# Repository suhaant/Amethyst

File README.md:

<div align="center">

### Smart wound care that catches infection early and treats it on the spot.

A wearable patch that senses infection before you can see it, scores the risk with an ML model,
has an AI agent check the evidence, and treats with **low-frequency ultrasound** and **405 nm violet light**.

**[Watch the 40-second film](remotion/renders/AmethystFilm.mp4)** · [How it works](#how-it-works) · [Quick start](#quick-start) · [The math](#the-math) · [Safety](#safety-in-three-layers)

</div>

---

## The problem

**60%** of diabetic foot ulcers become infected, and **15–20%** of diabetic foot infections end in amputation. Nerve damage removes pain, the body's warning sign, so infection often goes unnoticed until it's visible, and by then it's serious.

The early signs are measurable long before that. Infected wounds turn **alkaline** (healthy wounds sit at pH 4–6; infected ones at 7.5–9), get **warmer** and **wetter**, and bacteria use up the **glucose** in wound fluid. Amethyst watches for exactly those changes.

<sub>Sources: Diabetes Care; Nussbaum et al., *Value in Health* 2018. More in [`hardware/research/`](hardware/research/).</sub>

## How it works

```mermaid
flowchart LR
    P["Amethyst patch<br/>pH · moisture · 3× temp"] -->|"BLE, every 30 min"| S
    C["CGM<br/>blood glucose"] --> S
    S["FastAPI server<br/>POST /api/readings"] --> A{{"Gemini agent"}}
    A -->|tool| M["XGBoost model<br/>risk = likelihood × severity"]
    A -->|tool| D["Dosing engine<br/>tiers + safety caps"]
    A --> F["Notes, fact-checked<br/>in code"]
    S --> App["Expo app<br/>alert · therapy · trends"]
    S --> DB[("Databricks<br/>care record + dashboard")]
    D -->|"therapy command"| P
```

1. **Sense.** Every 30 minutes the patch reads wound pH, moisture (impedance) and temperature at three spots (wound edge, healthy reference skin, ambient). Blood glucose comes from the wearer's CGM.
2. **Predict.** An XGBoost model compares each reading with the patient's **own first-day baseline** and outputs a 0–100 risk score and a tier: monitor, watch, treat or intensive.
3. **Reason.** A **Gemini agent** calls the model and the dosing engine as tools, then writes a clinician-ready assessment. It covers the trend, sensor faults, signals that disagree with the model, its confidence, and whether a clinician should look. **It never invents a number:** risk and doses always come from our code, and its notes are fact-checked against the tool results.
4. **Treat.** In the treat tier the patch runs ultrasound to break up biofilm, then 405 nm light to kill bacteria. Lower tiers get gentle healing ultrasound and closer monitoring.
5. **Alert.** The app shows the patient their risk, trends and therapy. Every reading and assessment lands in Databricks for the care team.

## Results

Validated **leave-one-person-out** (16 folds): every person is scored by a model that never saw their data.

| | Random forest | **XGBoost** (shipped) |
|---|---|---|
| AUC | 0.976 | **0.978** |
| Brier skill score | 0.834 | **0.845** |
| Infected wounds detected | 100% | **100%** |
| Median hours from onset to alarm | 30.3 | **27.2** |
| False alarms, clean wounds | **0.3%** | 2.1% |
| Model size | 11.9 MB | **3.1 MB** |
| Time per prediction | 12.4 ms | **0.14 ms** |

We shipped XGBoost: it alarms **3.1 h earlier** and is **3.8× smaller** and **89× faster**, which matters on a wearable. The extra false alarms are absorbed by risk smoothing and the agent's review.

Which sensors matter most (AUC of each sensor on its own): **moisture 0.952** · temperature 0.933 · pH 0.917 · wound glucose 0.886 · blood glucose 0.650 · pH + temp + moisture together **0.976**.

> All results are on simulated data (see [limits](#honest-limits)). The full method is in [`docs/ml-pipeline.md`](docs/ml-pipeline.md).

## The math

**Training data.** No public dataset of continuous wound-sensor readings with infection labels exists, so we simulated one from **30+ published studies** and **real Dexcom glucose traces from 16 people** (PhysioNet):

$$600 \text{ wounds} \times 14 \text{ days} \times 48 \text{ readings/day} = 403{,}200 \text{ labelled readings}$$

**Features.** 5 signals × (6 h median, change vs. day-1 baseline, 6 h change, 24 h change, 24 h std) + 2 time-of-day terms = **27 features**.

**Risk = likelihood × severity.** Trained on cleanly separated data, the classifier is near-certain for *any* sustained shift. So we scale its probability by how far the signs have actually moved toward a full infection:

$$p = P(\text{warning}) + P(\text{infection})$$

$$s = \text{mean of the 3 largest of } \left\lbrace \frac{\Delta \text{pH}}{0.65},\ \ \frac{\Delta T}{1.6^{\circ}\text{C}},\ \ \frac{-\Delta \ln Z}{-\ln 0.65},\ \ \frac{-\Delta g / g_0}{0.40}\right\rbrace$$

Each Δ is a 2 h median minus the patient's day-1 baseline. The denominators are a full infection's average effect in the simulator: pH +0.65, temperature +1.6 °C, impedance −35%, wound glucose −40%. Each term is clipped to [0, 1.25] and *s* to [0, 1]. Using the top 3 of 4 means a wound whose pH doesn't rise, which happens in real infections, still scores. The score is then smoothed so one noisy reading can't trigger treatment (τ = 3 h, Δt = 0.5 h):

$$R_t = R_{t-1} + \alpha(100 p_t s_t - R_{t-1}), \qquad \alpha = \frac{0.5}{3 + 0.5} \approx 0.143$$

**Tiers** use 10-point hysteresis: each is entered at its threshold and left only 10 points below it, so the device doesn't flicker.

| Tier | Enter at | Therapy each 8 h session (3/day) |
|---|---|---|
| 0 · Monitor | — | 1.5 MHz healing ultrasound, 6.7 min (20 min/day ÷ 3) |
| 1 · Watch | 30 | Healing ultrasound + closer monitoring |
| 2 · Treat | 55 | Ultrasound to break biofilm → 405 nm light |
| 3 · Intensive | 80 | Same, scaled up toward the caps |

**Light dose** (treat tier and above) at 10 mW/cm², with the 36 J/cm² daily cap split over 3 sessions:

$$x = \text{clip}\left(\frac{R - 30}{60}, 0, 1\right), \qquad E = 12x \ \text{J/cm}^2, \qquad t = \frac{E}{0.010 \ \text{W/cm}^2}$$

**Ultrasound** (treat tier and above), run before the light:

$$y = \text{clip}\left(\frac{R - 55}{35}, 0, 1\right), \qquad t_{\text{US}} = \max(4,\ 10y) \ \text{min}, \qquad I = 0.1 + 0.4y \ \text{W/cm}^2$$

| Risk *R* | Light | Ultrasound |
|---|---|---|
| 55 (enters treat) | 5 J/cm² → **8.3 min** | 4 min at 0.10 W/cm² |
| 72.5 | 8.5 J/cm² → **14.2 min** | 5 min at 0.30 W/cm² |
| 100 | 12 J/cm² → **20 min** (3 × 12 = 36 J/cm²/day cap) | 10 min at 0.50 W/cm² |

## The AI agent

[`wound_agent/`](wound_agent/) wraps the model and dosing in three tools: `get_sensor_history` → `predict_infection` → `plan_treatment`. The LLM writes structured notes: `summary`, `trend`, `reasoning`, `data_quality_flags`, `conflicting_signals`, `recommend_clinician_review` and `confidence`.

- **Gemini by default.** Gemini 3.8 Flash with low thinking takes about 5 s and about $0.005 per assessment. `GEMINI_MODEL=gemini-3.1-pro-preview` with `GEMINI_THINKING=high` gives maximum care. OpenRouter and Claude Opus also work (`AGENT_PROVIDER=gemini|openrouter|claude`).
- **Fact-checked.** After the agent writes, code checks its notes against the tool results (risk score, tier, lifted patch, clinician review) and asks for one correction if anything is off.
- **Knows what to distrust.** It's told each sensor's standalone accuracy, that infections don't always raise pH, and how hysteresis works. In testing it caught a 43 °C reading as a sensor fault rather than a fever, and blamed a risk jump on a meal-time glucose spike while the wound sensors stayed healthy.
- **Never blocks the demo.** With no API key, the same model and dosing run and a rule-based summary stands in.

## Hardware

A reusable **30 × 40 mm, 4-layer** pod that clips onto a disposable hydrogel pad. [Full spec →](hardware/docs/board-spec.md)

| Block | Parts |
|---|---|
| Radio + MCU | Raytac MDBT42Q (nRF52832), Bluetooth LE |
| Temperature | 3× TMP117: wound edge, reference skin, ambient |
| Moisture | 1 kHz square wave through a 47 kΩ reference into the pad electrodes, read as impedance (no dedicated chip) |
| pH | AD8603 buffer on the working electrode |
| Light | 6× 405 nm LEDs, TPS61165 constant-current boost, PWM dimming |
| Ultrasound | 15 mm 30 kHz piezo disc, TPS61040 boost (5–10 V) + DRV8837 H-bridge + 4.7 mH resonant inductor |
| Power | Single LiPo, MCP73831 charger, AP2112K 3.3 V regulator |
| Extras | Pad-ID resistor, button for a daily pain/odour check-in, SWD debug pads |

**Generated, not drawn.** One Python file ([`design.py`](hardware/kicad/gen/design.py)) generates the schematic, places every part, autoroutes all **178 connections** and runs KiCad's electrical and design-rule checks in one command.

**Power and heat budget** ([details](hardware/experiments/out/power_thermal_results.md)):
- Sensing averages **~22 µA**, which is about **60 days on a 40 mAh cell**.
- At 10 mW/cm² of light, skin reaches 37.3 °C, or **38.7 °C on a poorly perfused diabetic foot**, including the LEDs' own heat. Both stay under our 41 °C ceiling.
- Doubling to 20 mW/cm² would hit 43.4 °C, so we didn't.

## Safety in three layers

| Layer | What it enforces |
|---|---|
| **1 · Software** ([`risk_to_dose.py`](risk_to_dose.py)) | Dose caps, tier hysteresis, no therapy when impedance > 150 kΩ (patch lifted) |
| **2 · Firmware** ([`firmware/`](firmware/)) | The same caps again, whatever the phone asks: 10 mW/cm², 36 J/cm²/day, 10 min of pulsed ultrasound (500 ms on / off), stop at 41 °C, and no session without a pad attached and on the skin, a working wound sensor, and battery > 3.5 V |
| **3 · Hardware** | Every TMP117 alert pin feeds AND gates on the light and ultrasound enables. At **42 °C**, therapy cuts out **even if the firmware has crashed** |

## Quick start

**Python 3.12+** (Adam's pinned numpy 2.5 and xgboost 3.4 need it).

```bash
python -m venv .venv
source .venv/bin/activate          # Windows: .venv\Scripts\activate
pip install -r requirements.txt
cp .env.example .env               # add GEMINI_API_KEY (or OPENROUTER_ / ANTHROPIC_API_KEY)
```

**Run the agent on a simulated wound:**

```bash
python main.py -v --scenario infected        # healthy | early_infection | infected | sensor_fault | patch_lifted
python main.py --history sample_data/simulated_wound_history.csv
python main.py --offline                     # model + dosing only, no LLM
```

**Live demo + hardware API** (then open http://localhost:8000):

```bash
python demo_ui/server.py
python demo_ui/send_reading.py --scenario infection --count 8 --every 3    # pretend to be the patch
```

| Endpoint | What |
|---|---|
| `POST /api/readings` | One patch reading in → risk, tier and therapy plan out |
| `GET /api/state` | Latest assessment (the app polls this) |
| `GET /api/events` | Server-sent events for every pipeline step |
| `POST /api/reset` | New patient with a fresh 24 h baseline |
| `GET /docs` | Interactive API docs |

**Phone app** (Expo Go):

```bash
cd app && npm install && npx expo start      # add --tunnel on campus Wi-Fi
```

**Firmware tests** (simulated board) and **board build** (KiCad 10):

```bash
cd firmware && make test && make arm-check
cd hardware/kicad && ./build.sh              # about 6 min with autorouting; --no-route for seconds
```

**Databricks care record** (landing from the `databricks` branch; design in [`docs/superpowers/specs/`](docs/superpowers/specs/)):

```bash
python main.py --databricks                  # readings + assessments to Databricks, care-team dashboard
```

**Film:**

```bash
cd remotion && npm install && npm run dev
```

**Tests:**

```bash
python -m pytest
```

## Repo map

| Path | What |
|---|---|
| [`wound_agent/`](wound_agent/) · [`main.py`](main.py) | AI agent: tools, prompts, providers, fact check, CLI |
| [`predict.py`](predict.py) · [`risk_to_dose.py`](risk_to_dose.py) · [`model/`](model/) | Trained XGBoost model, risk score, dosing engine |
| [`generate_data.py`](generate_data.py) · [`train_*.py`](train_final.py) · [`compare_models.py`](compare_models.py) | Simulator, training, RF vs. XGBoost, validation ([write-up](docs/ml-pipeline.md)) |
| [`research/`](research/) · [`hardware/research/`](hardware/research/) | Literature values for every simulator parameter, signal and dose, with sources |
| [`demo_ui/`](demo_ui/) | FastAPI server, hardware API, animated live demo |
| [`app/`](app/) | Expo companion app: Pair, Home, Alert, Therapy, Trends |
| [`hardware/`](hardware/) · [`firmware/`](firmware/) | KiCad board generator + board, C firmware with Zephyr port |
| [`remotion/`](remotion/) | Demo film and brand assets |
| [`tests/`](tests/) | Pipeline tests: scenarios, tiers, dose caps, interlock |

## Honest limits

- **Simulated training data.** The model has never seen a real wound. Retrain on real patch data before any clinical use.
- **Prototype doses** from published studies, not a validated medical protocol.
- **The board is designed and autorouted but not yet fabricated,** and the firmware has only run on a simulated board. Light and ultrasound intensity at the wound are estimates until measured.
- **Not all on the board yet.** The board's ultrasound runs at 30 kHz (within the 20–40 kHz range of clinical wound devices). The 1.5 MHz healing mode and wound-fluid glucose sensing aren't on this board yet.
- **Combining light and ultrasound** is backed by lab (in-vitro) studies so far.

## Team

Built at **WolfHacks 2026** by:
- **Adam Rakhmanov:** ML model, simulator, dosing, demo server.
- **Anay Vaidya:** hardware, firmware, Databricks.
- **Aarush:** app and film.
- **Suhaan Temkar:** AI agent.

<sub>Glucose data: BIG IDEAs Lab Glycemic Variability and Wearable Device Data v1.1.3, PhysioNet, ODC-By 1.0.</sub>

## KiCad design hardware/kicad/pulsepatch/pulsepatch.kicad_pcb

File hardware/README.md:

# PulsePatch hardware

Hardware for PulsePatch, a wearable wound patch that senses temperature, moisture and pH and can drive 405 nm light and low-frequency ultrasound. Owner: Anay. Lives on the `KiCAD` branch until it is ready for `main`.

## Layout

| Folder | What is in it |
|---|---|
| `context/` | The team synopsis (`Wolfhacks.pdf`) and the note on light plus ultrasound evidence |
| `research/raw/` | Literature reviews: `A-clinical-signals.md` (which wound signals are worth sensing) and `C-therapy-hardware.md` (light and ultrasound doses, parts, safety limits) |
| `experiments/` | Scripts and results: KiCad library scan, board packing, power and heat budget |
| `docs/board-spec.md` | The approved board spec and the list of things not verified yet |
| `kicad/gen/` | The generator. `design.py` is the single source of truth for parts, connections and placement |
| `kicad/pulsepatch/` | Generated KiCad project: schematic, board, check reports, renders |

## Build the board

Needs KiCad 10 at `/Applications/KiCad` and Java (for the autorouter).

```
cd hardware/kicad
./build.sh              # full build with autorouting, about 6 minutes
./build.sh --no-route   # placed, unrouted board in seconds
```

Then open `kicad/pulsepatch/pulsepatch.kicad_pro` in KiCad.

The build writes `erc.rpt` (schematic check), `drc.rpt` (board check), `pulsepatch-schematic.pdf`, and `render-top.png` / `render-bottom.png` into `kicad/pulsepatch/`.

## Changing the design

Edit `kicad/gen/design.py` and rebuild. The schematic and board are regenerated from it every time, so edits made by hand in the KiCad editor are lost on the next build. Once the design settles and hand routing starts, stop running the build and treat the KiCad files as the source.

## Status

See `docs/board-spec.md` for what is and is not verified. The board is autorouted and has not been reviewed by a person or fabricated.

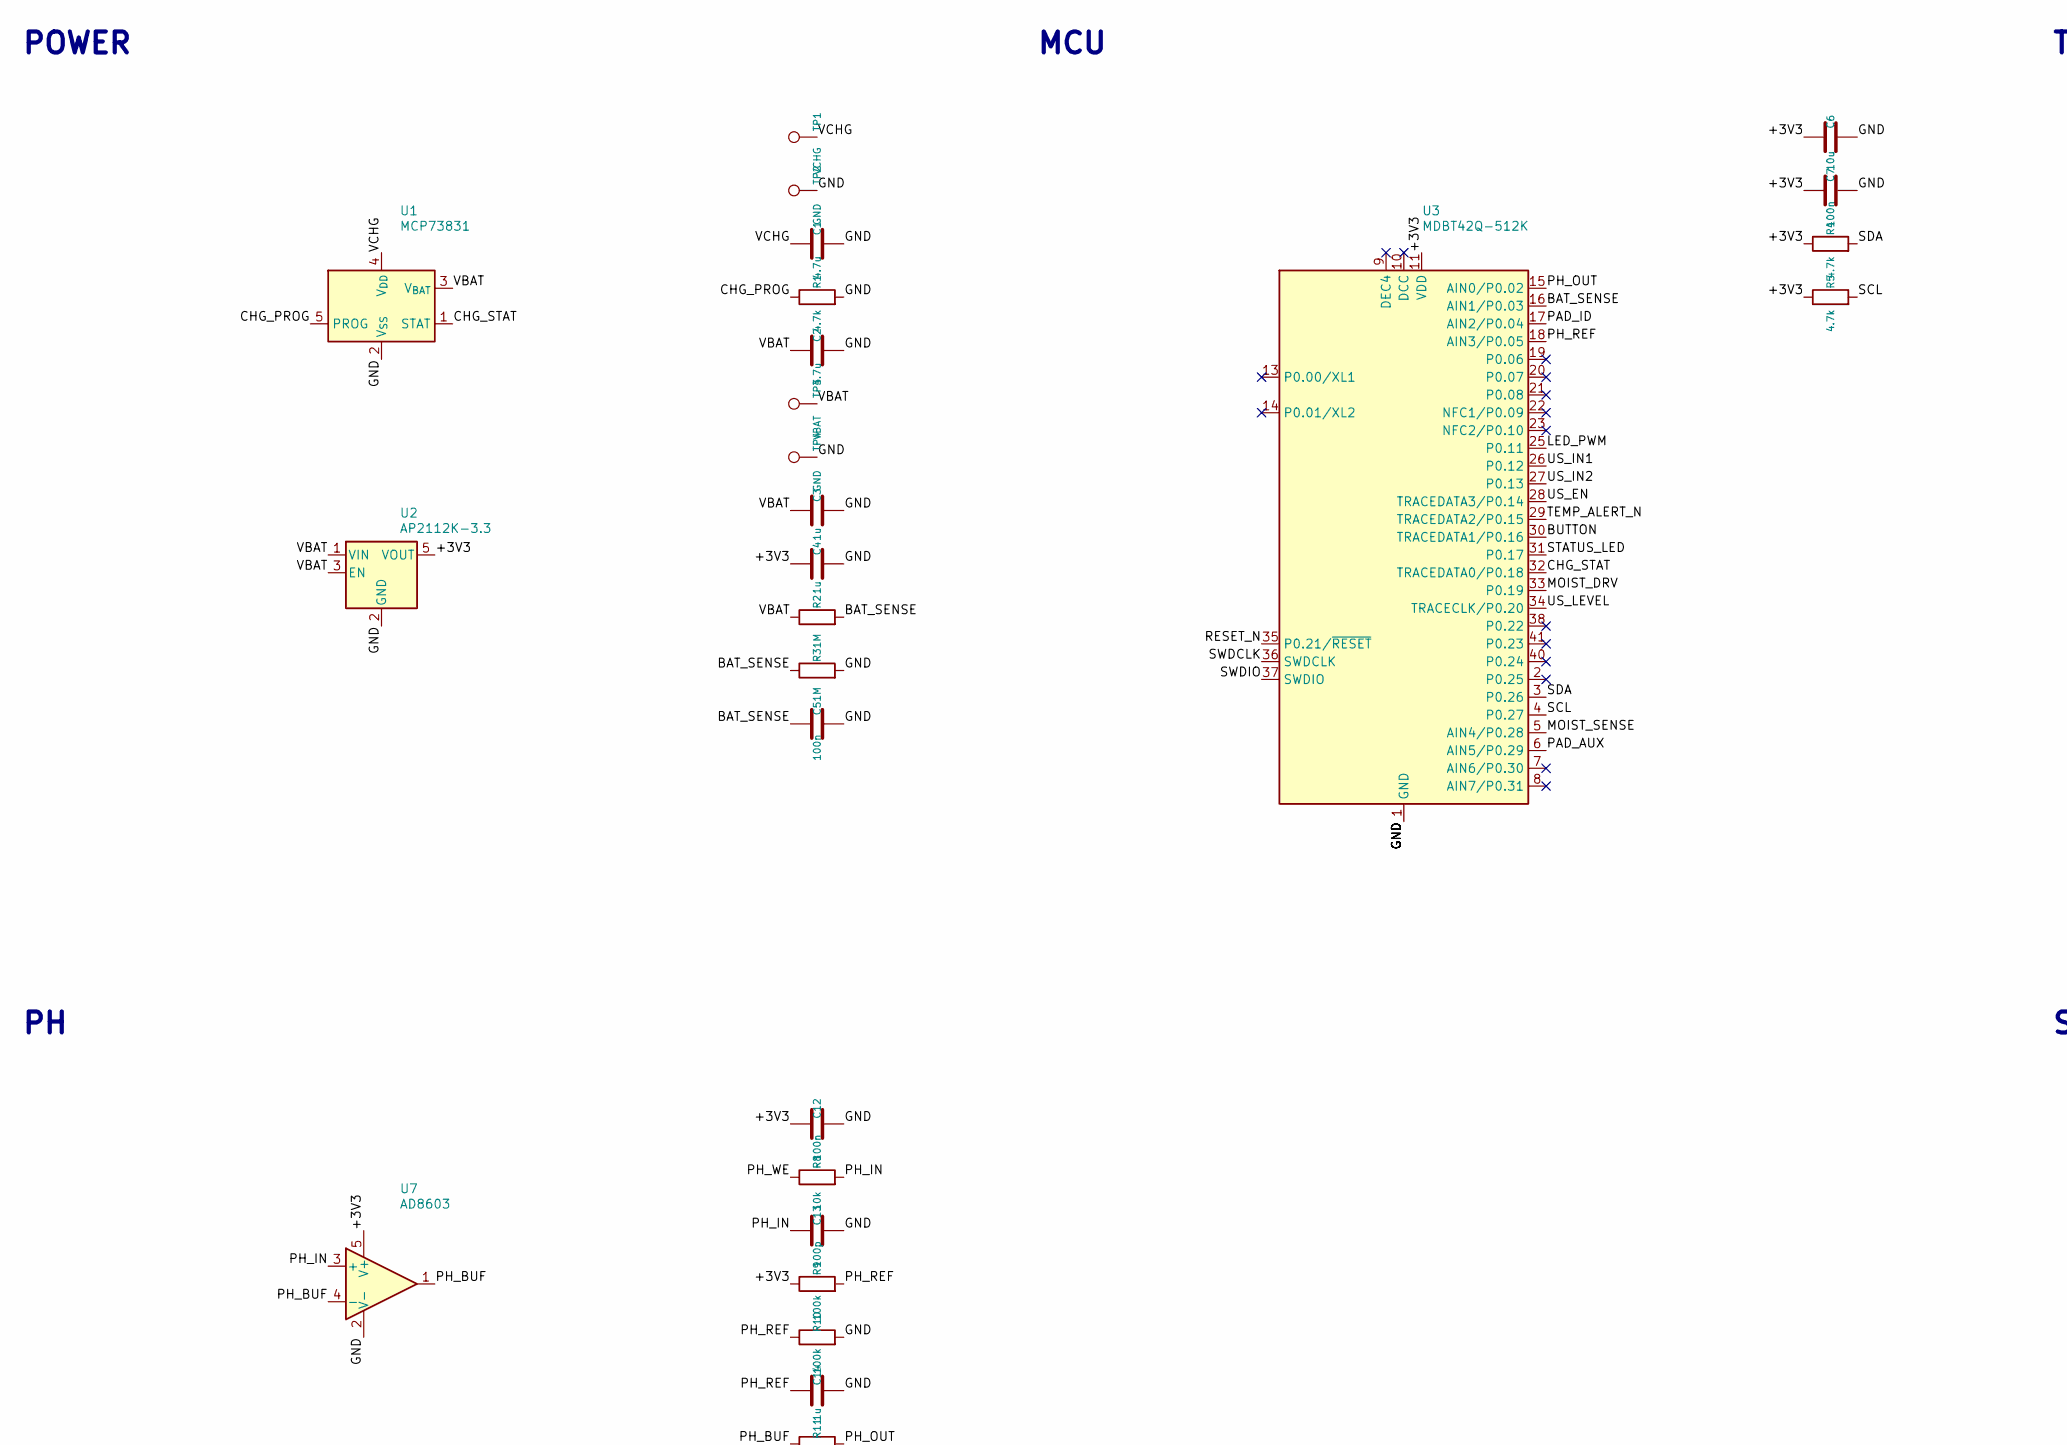
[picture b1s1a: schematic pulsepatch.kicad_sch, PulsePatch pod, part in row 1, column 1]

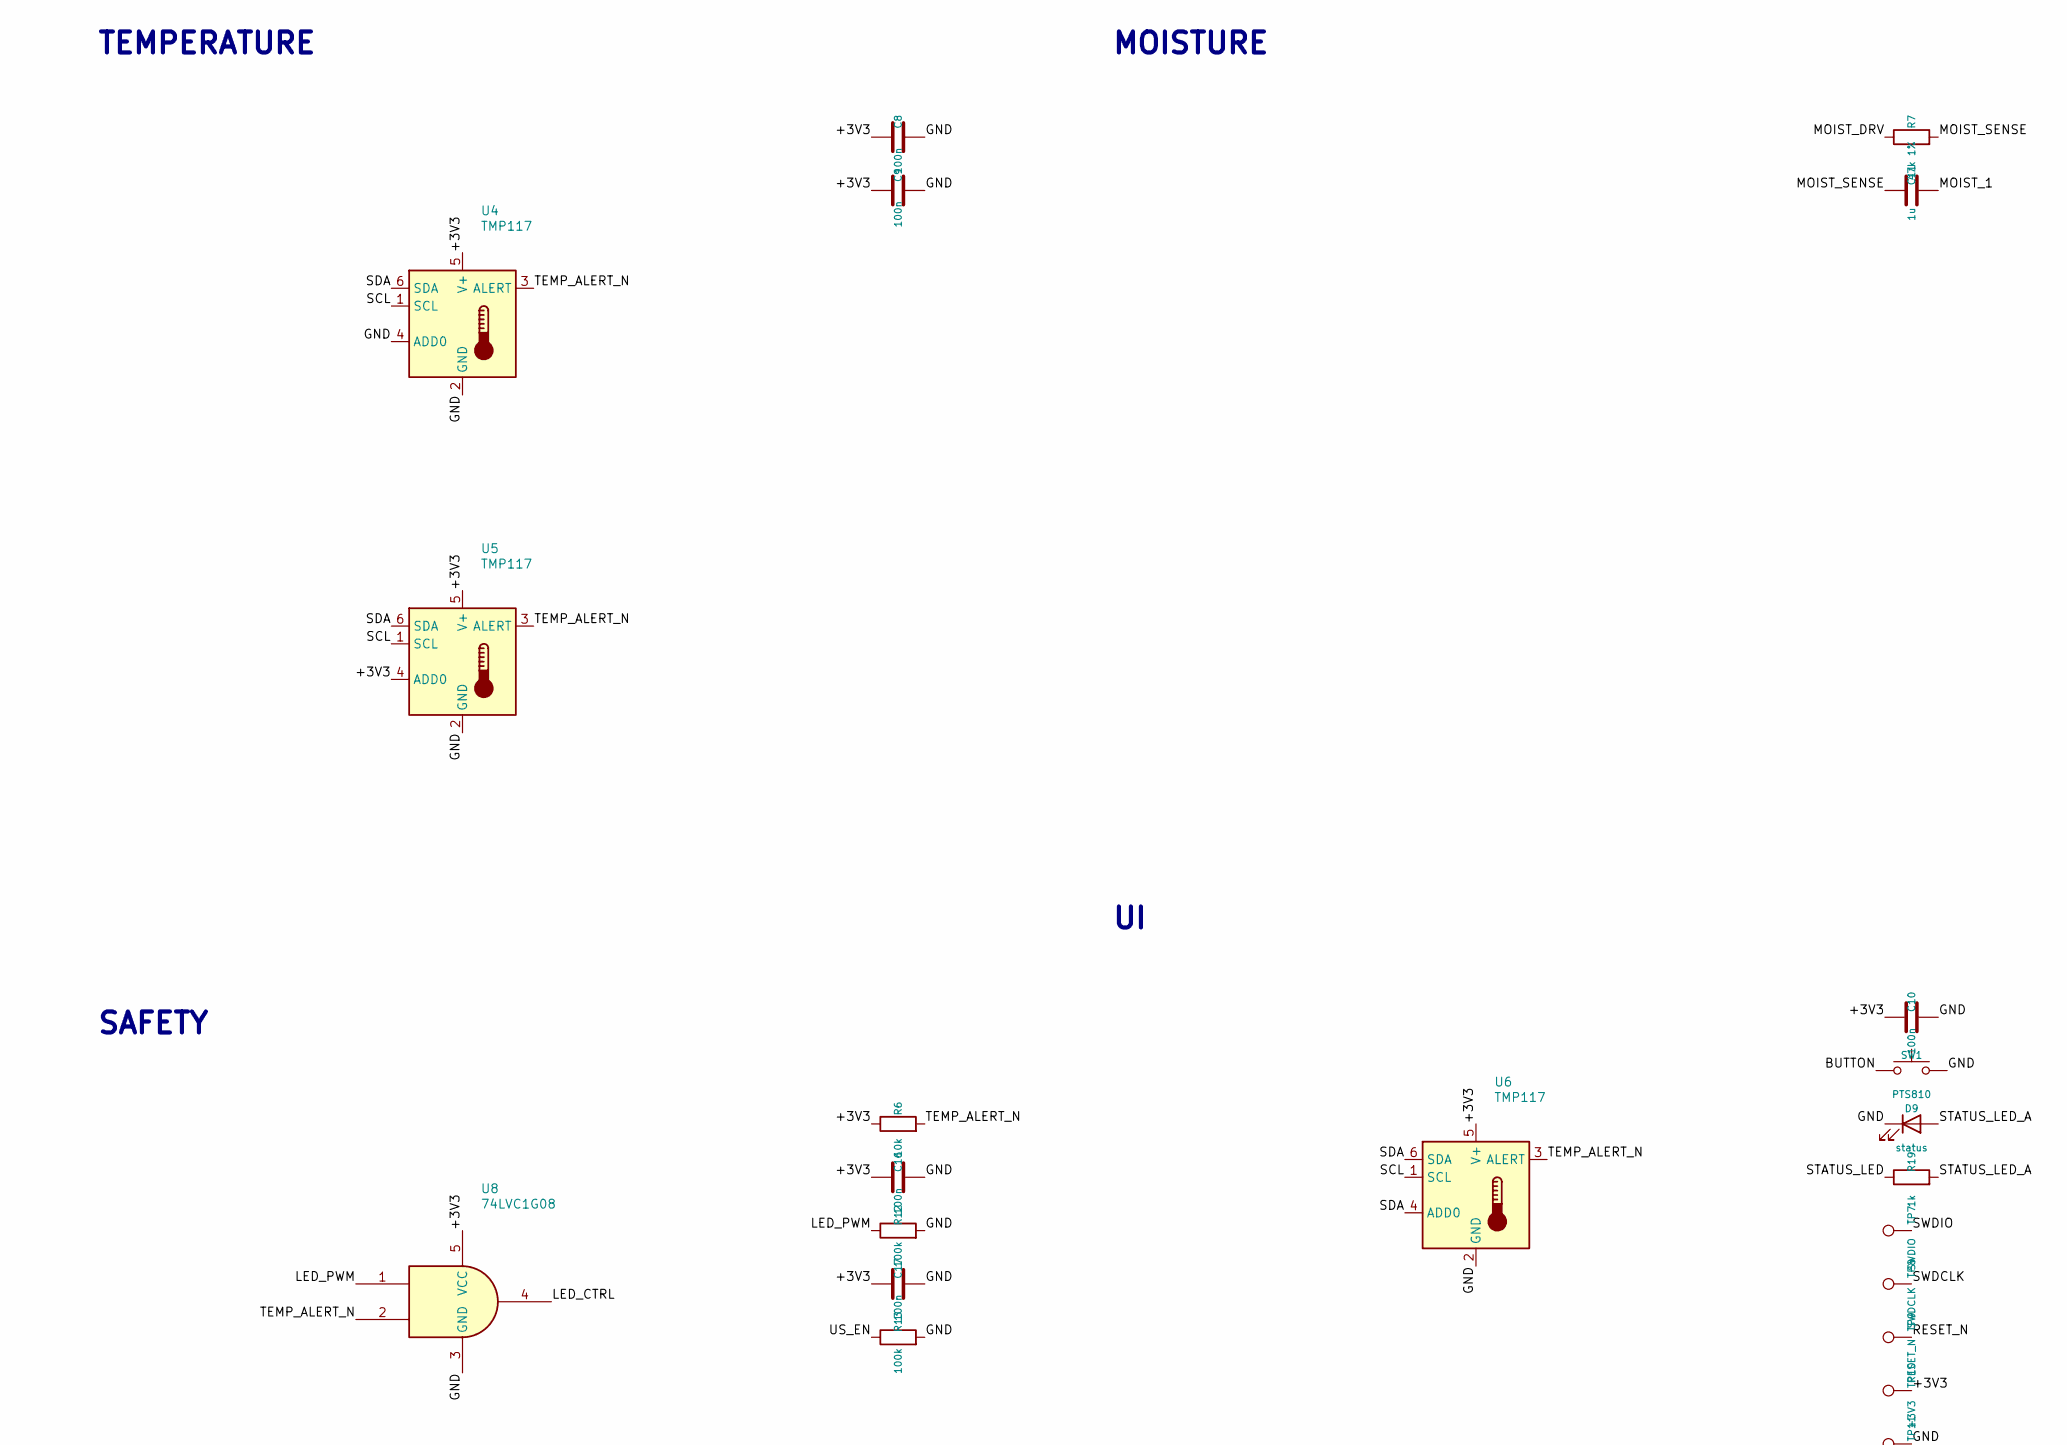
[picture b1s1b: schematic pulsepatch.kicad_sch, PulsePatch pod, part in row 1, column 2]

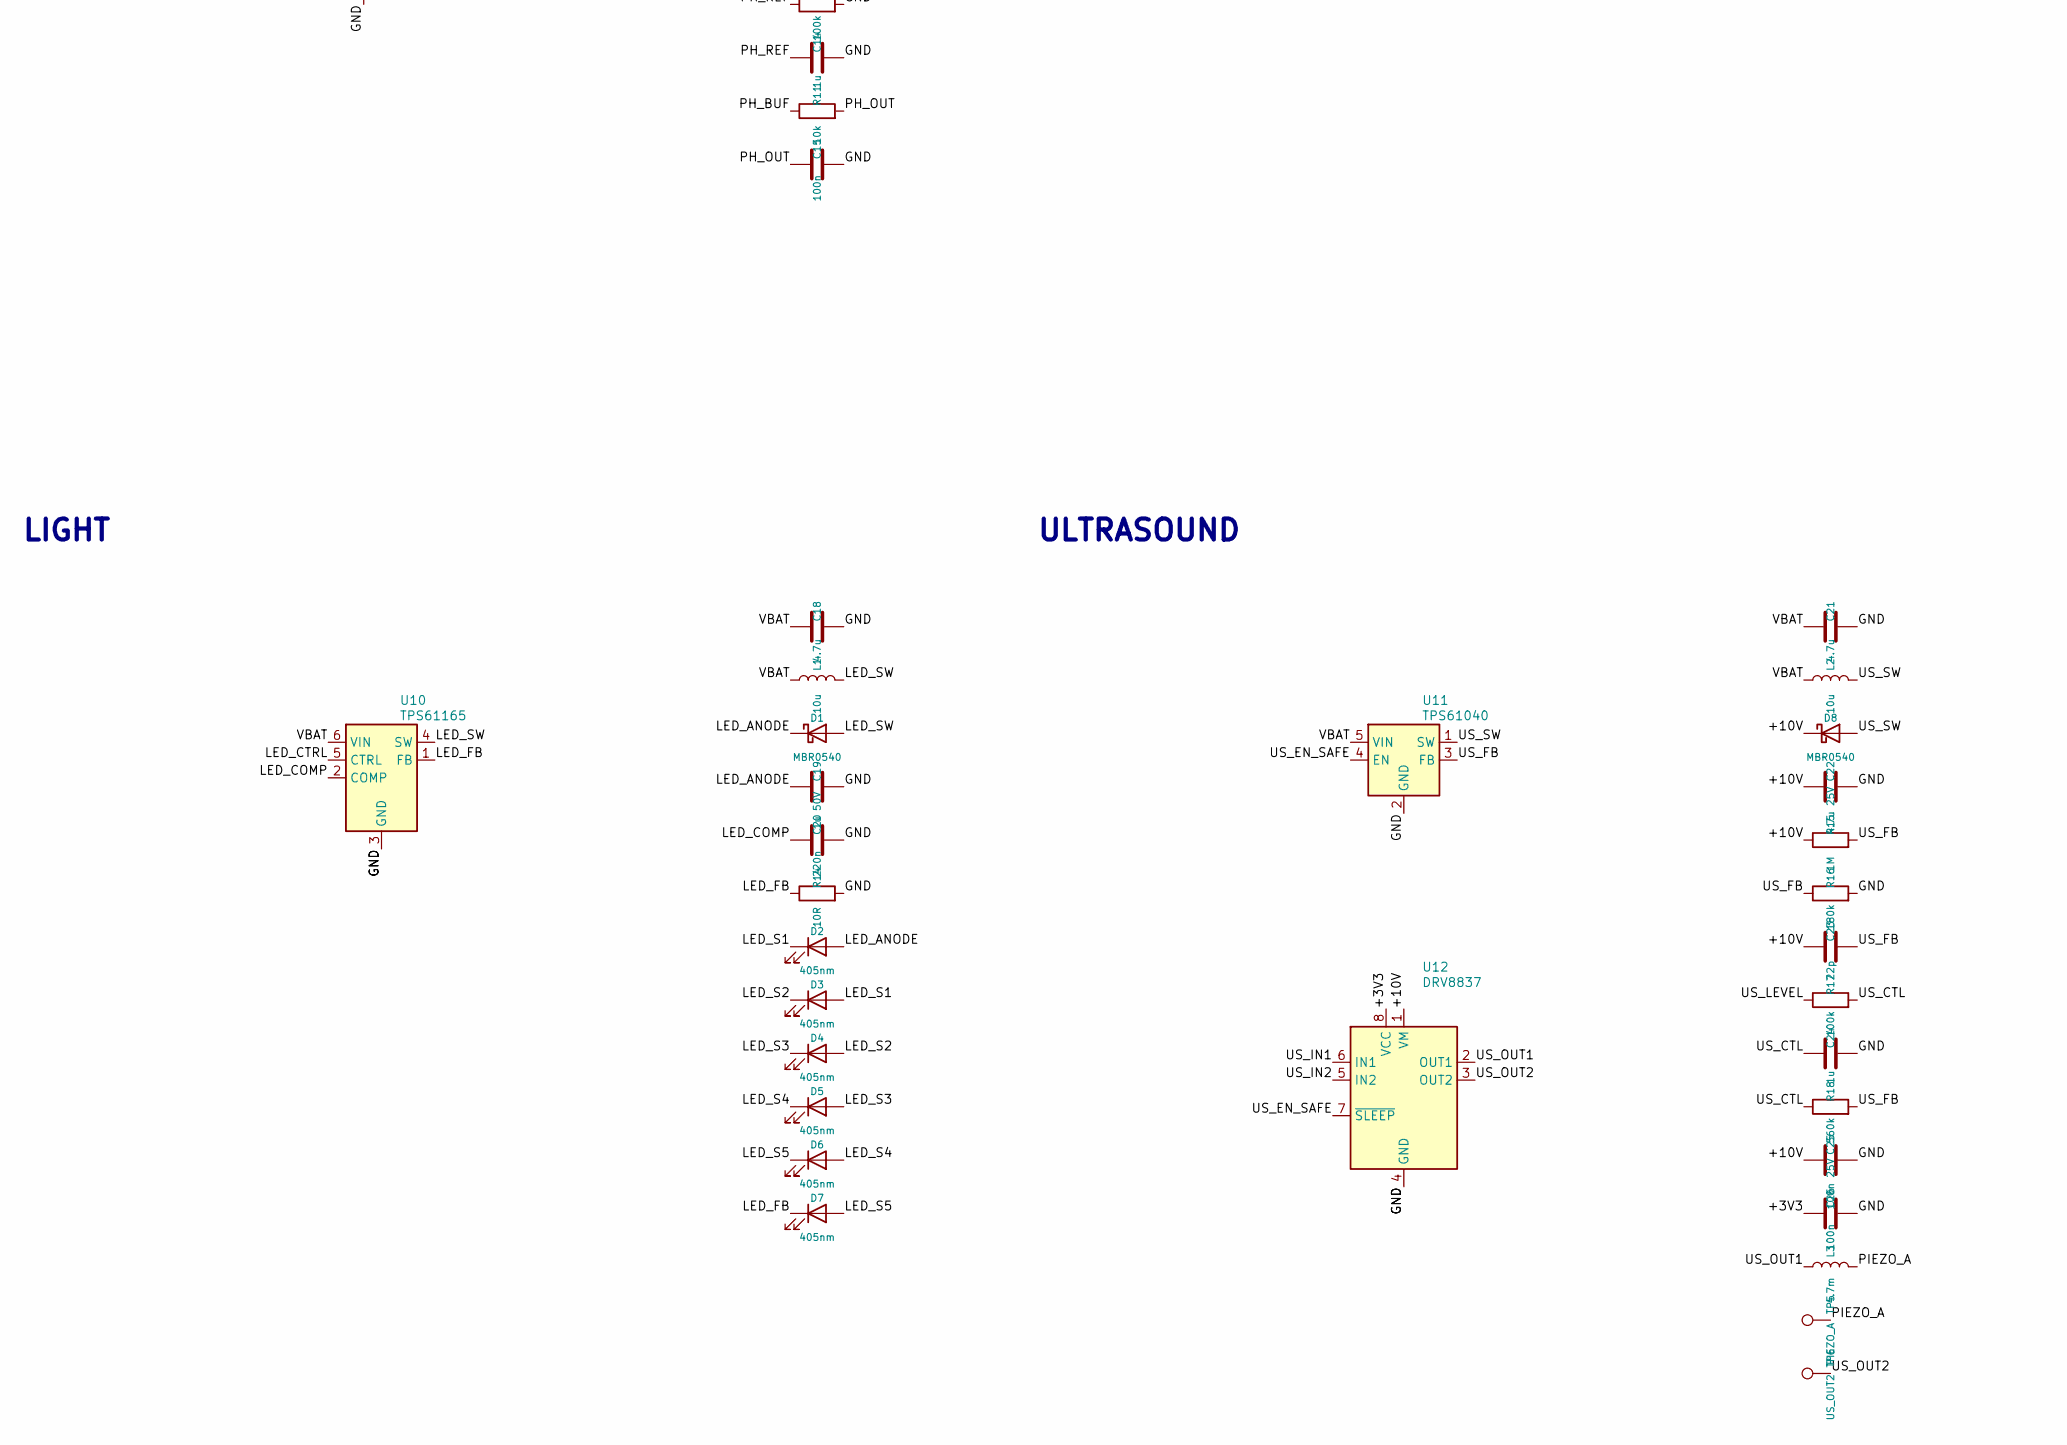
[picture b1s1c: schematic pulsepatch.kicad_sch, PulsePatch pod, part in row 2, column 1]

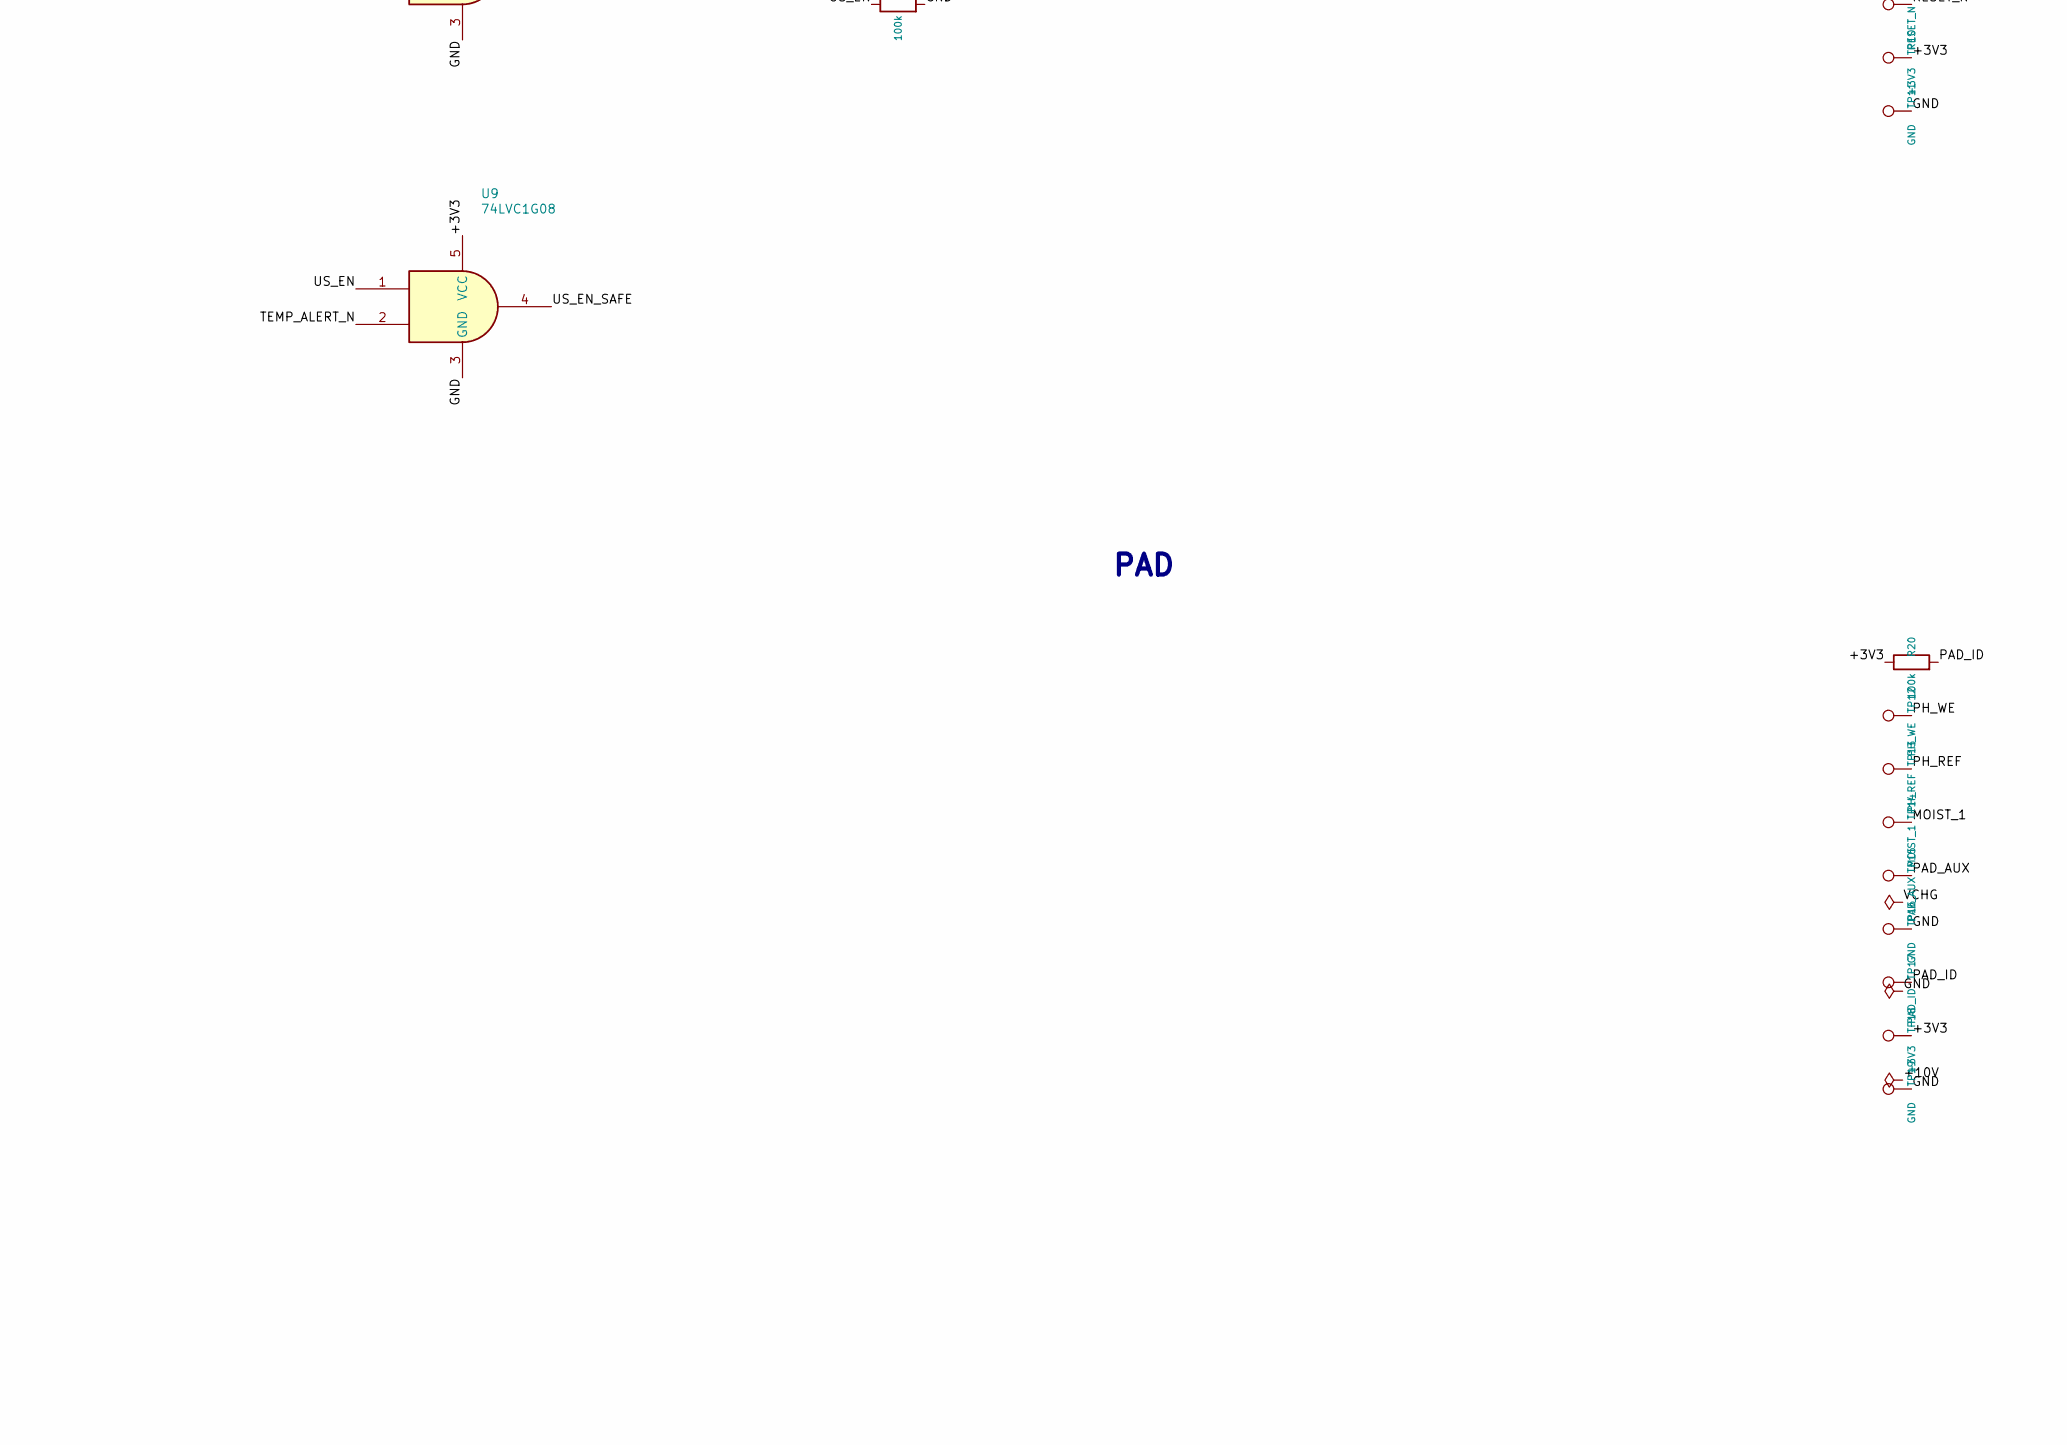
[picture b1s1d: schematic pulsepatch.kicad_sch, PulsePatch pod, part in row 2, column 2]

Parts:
C1, C2, C18, C21: 4.7u; C_0603_1608Metric
C3, C4, C11, C14, C24: 1u; C_0402_1005Metric
C5, C7, C8, C9, C10, C12, C15, C16, C17, C26: 100n; C_0402_1005Metric
C6: 10u; C_0603_1608Metric
C13: 100p; C_0402_1005Metric
C19: 1u 50V; C_0805_2012Metric
C20: 220n; C_0402_1005Metric
C22: 4.7u 25V; C_0805_2012Metric
C23: 22p; C_0402_1005Metric
C25: 100n 25V; C_0402_1005Metric
D1, D8: MBR0540; D_SOD-123
D2, D3, D4, D5, D6, D7: 405nm; LED_Cree-XP
D9: status; LED_0603_1608Metric
L1, L2: 10u; L_Taiyo-Yuden_NR-30xx
L3: 4.7m; L_6.3x6.3_H3
R1, R4, R5: 4.7k; R_0402_1005Metric
R2, R3, R15: 1M; R_0402_1005Metric
R6, R8, R11: 10k; R_0402_1005Metric
R7: 47k 1%; R_0402_1005Metric
R9, R10, R12, R13, R17, R20: 100k; R_0402_1005Metric
R14: 10R; R_0402_1005Metric
R16: 180k; R_0402_1005Metric
R18: 560k; R_0402_1005Metric
R19: 1k; R_0402_1005Metric
SW1: PTS810; SW_SPST_PTS810
TP1: VCHG; TestPoint_Pad_1.5x1.5mm
TP2, TP4, TP11: GND; TestPoint_Pad_1.5x1.5mm
TP3: VBAT; TestPoint_Pad_1.5x1.5mm
TP5: PIEZO_A; TestPoint_Pad_1.5x1.5mm
TP6: US_OUT2; TestPoint_Pad_1.5x1.5mm
TP7: SWDIO; TestPoint_Pad_1.5x1.5mm
TP8: SWDCLK; TestPoint_Pad_1.5x1.5mm
TP9: RESET_N; TestPoint_Pad_1.5x1.5mm
TP10: +3V3; TestPoint_Pad_1.5x1.5mm
TP12: PH_WE; TestPoint_Pad_2.0x2.0mm
TP13: PH_REF; TestPoint_Pad_2.0x2.0mm
TP14: MOIST_1; TestPoint_Pad_2.0x2.0mm
TP15: PAD_AUX; TestPoint_Pad_2.0x2.0mm
TP16, TP19: GND; TestPoint_Pad_2.0x2.0mm
TP17: PAD_ID; TestPoint_Pad_2.0x2.0mm
TP18: +3V3; TestPoint_Pad_2.0x2.0mm
U1: MCP73831; SOT-23-5
U2: AP2112K-3.3; SOT-23-5
U3: MDBT42Q-512K; Raytac_MDBT42Q
U4, U5, U6: TMP117; WSON-6-1EP_2x2mm_P0.65mm_EP1x1.6mm
U7: AD8603; TSOT-23-5
U8, U9: 74LVC1G08; SOT-23-5
U10: TPS61165; WSON-6-1EP_2x2mm_P0.65mm_EP1x1.6mm
U11: TPS61040; SOT-23-5
U12: DRV8837; WSON-8-1EP_2x2mm_P0.5mm_EP0.9x1.6mm

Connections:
/+3V3: C4.1, C6.1, C7.1, C8.1, C9.1, C10.1, C12.1, C16.1, C17.1, C26.1, R4.1, R5.1, R6.1, R9.1, R20.1, TP10.1, TP18.1, U2.5 (VOUT), U3.11 (VDD), U4.5 (V+), U5.4 (ADD0), U5.5 (V+), U6.5 (V+), U7.5 (V+), U8.5 (VCC), U9.5 (VCC), U12.8 (VCC)
/+10V: C22.1, C23.1, C25.1, D8.1 (K), R15.1, U12.1 (VM)
/BAT_SENSE: C5.1, R2.2, R3.1, U3.16 (AIN1/P0.03)
/BUTTON: SW1.1, U3.30 (TRACEDATA1/P0.16)
/CHG_PROG: R1.1, U1.5 (PROG)
/CHG_STAT: U1.1 (STAT), U3.32 (TRACEDATA0/P0.18)
/GND: C1.2, C2.2, C3.2, C4.2, C5.2, C6.2, C7.2, C8.2, C9.2, C10.2, C12.2, C13.2, C14.2, C15.2, C16.2, C17.2, C18.2, C19.2, C20.2, C21.2, C22.2, C24.2, C25.2, C26.2, D9.1 (K), R1.2, R3.2, R10.2, R12.2, R13.2, R14.2, R16.2, SW1.2, TP2.1, TP4.1, TP11.1, TP16.1, TP19.1, U1.2 (V_{SS}), U2.2 (GND), U3.1 (GND), U3.12 (GND), U3.24 (GND), U3.39 (GND), U4.2 (GND), U4.4 (ADD0), U5.2 (GND), U6.2 (GND), U7.2 (V-), U8.3 (GND), U9.3 (GND), U10.3 (GND), U10.7 (GND), U11.2 (GND), U12.4 (GND), U12.9 (GND)
/LED_ANODE: C19.1, D1.1 (K), D2.2 (A)
/LED_COMP: C20.1, U10.2 (COMP)
/LED_CTRL: U8.4, U10.5 (CTRL)
/LED_FB: D7.1 (K), R14.1, U10.1 (FB)
/LED_PWM: R12.1, U3.25 (P0.11), U8.1
/LED_S1: D2.1 (K), D3.2 (A)
/LED_S2: D3.1 (K), D4.2 (A)
/LED_S3: D4.1 (K), D5.2 (A)
/LED_S4: D5.1 (K), D6.2 (A)
/LED_S5: D6.1 (K), D7.2 (A)
/LED_SW: D1.2 (A), L1.2, U10.4 (SW)
/MOIST_1: C11.2, TP14.1
/MOIST_DRV: R7.1, U3.33 (P0.19)
/MOIST_SENSE: C11.1, R7.2, U3.5 (AIN4/P0.28)
/PAD_AUX: TP15.1, U3.6 (AIN5/P0.29)
/PAD_ID: R20.2, TP17.1, U3.17 (AIN2/P0.04)
/PH_BUF: R11.1, U7.1, U7.4 (-)
/PH_IN: C13.1, R8.2, U7.3 (+)
/PH_OUT: C15.1, R11.2, U3.15 (AIN0/P0.02)
/PH_REF: C14.1, R9.2, R10.1, TP13.1, U3.18 (AIN3/P0.05)
/PH_WE: R8.1, TP12.1
/PIEZO_A: L3.2, TP5.1
/RESET_N: TP9.1, U3.35 (P0.21/~RESET)
/SCL: R5.2, U3.4 (P0.27), U4.1 (SCL), U5.1 (SCL), U6.1 (SCL)
/SDA: R4.2, U3.3 (P0.26), U4.6 (SDA), U5.6 (SDA), U6.4 (ADD0), U6.6 (SDA)
/STATUS_LED: R19.1, U3.31 (P0.17)
/STATUS_LED_A: D9.2 (A), R19.2
/SWDCLK: TP8.1, U3.36 (SWDCLK)
/SWDIO: TP7.1, U3.37 (SWDIO)
/TEMP_ALERT_N: R6.2, U3.29 (TRACEDATA2/P0.15), U4.3 (ALERT), U5.3 (ALERT), U6.3 (ALERT), U8.2, U9.2
/US_CTL: C24.1, R17.2, R18.1
/US_EN: R13.1, U3.28 (TRACEDATA3/P0.14), U9.1
/US_EN_SAFE: U9.4, U11.4 (EN), U12.7 (~SLEEP)
/US_FB: C23.2, R15.2, R16.1, R18.2, U11.3 (FB)
/US_IN1: U3.26 (P0.12), U12.6 (IN1)
/US_IN2: U3.27 (P0.13), U12.5 (IN2)
/US_LEVEL: R17.1, U3.34 (TRACECLK/P0.20)
/US_OUT1: L3.1, U12.2 (OUT1)
/US_OUT2: TP6.1, U12.3 (OUT2)
/US_SW: D8.2 (A), L2.2, U11.1 (SW)
/VBAT: C2.1, C3.1, C18.1, C21.1, L1.1, L2.1, R2.1, TP3.1, U1.3 (V_{BAT}), U2.1 (VIN), U2.3 (EN), U10.6 (VIN), U11.5 (VIN)
/VCHG: C1.1, TP1.1, U1.4 (V_{DD})

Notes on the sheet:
POWER
MCU
TEMPERATURE
MOISTURE
SAFETY
LIGHT
ULTRASOUND
PAD

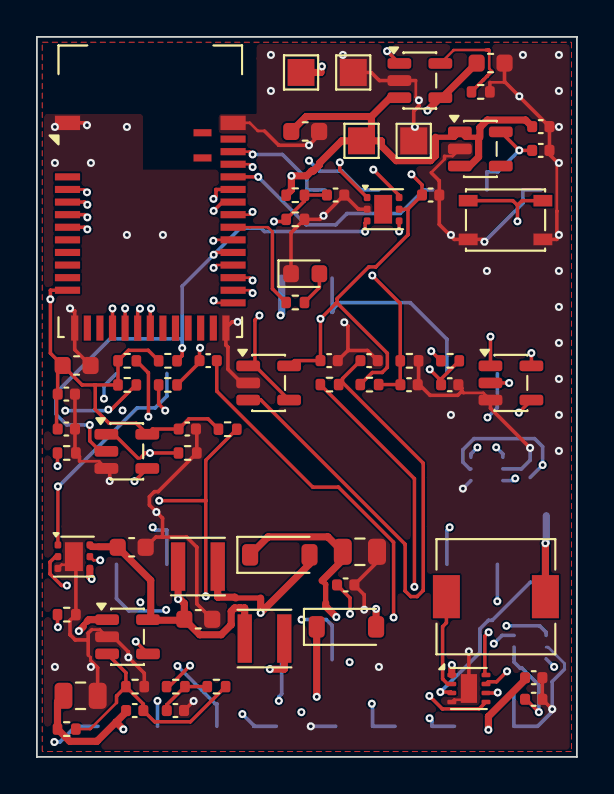
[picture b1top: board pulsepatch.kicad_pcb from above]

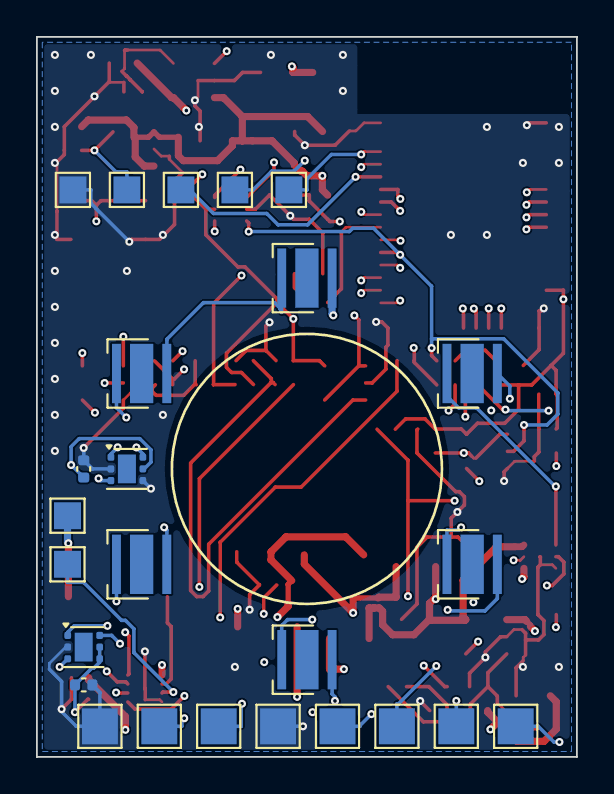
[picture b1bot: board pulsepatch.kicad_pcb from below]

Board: 4 copper layers, 30.0 x 40.0 mm, 90 parts (25 on the bottom side), 49 nets.

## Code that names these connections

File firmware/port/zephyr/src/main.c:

/* PulsePatch on the nRF52832 with the nRF Connect SDK (Zephyr).
 *
 * NOT BUILT OR RUN YET. This file implements pp_hal.h with Zephyr drivers and runs the same core
 * that the host tests exercise. It was written from the documented APIs without the SDK installed,
 * so expect to fix small things on the first build.
 */
#include <string.h>

#include <zephyr/bluetooth/bluetooth.h>
#include <zephyr/device.h>
#include <zephyr/drivers/adc.h>
#include <zephyr/drivers/gpio.h>
#include <zephyr/drivers/i2c.h>
#include <zephyr/drivers/pwm.h>
#include <zephyr/kernel.h>
#include <zephyr/sys/printk.h>
#include <zephyr/sys/util.h>

#include <bluetooth/services/nus.h>

#include "app.h"
#include "pp_hal.h"

#define USER DT_PATH(zephyr_user)
#define US_PERIOD_NS 33333u                  /* 30 kHz: tune to the disc's loaded resonance */
#define LED_PERIOD_US 1000u
#define LEVEL_PERIOD_US 1000u
#define MOISTURE_CYCLES 16

static const struct device *const i2c = DEVICE_DT_GET(DT_NODELABEL(i2c0));
static const struct adc_dt_spec adc[] = {
	ADC_DT_SPEC_GET_BY_IDX(USER, 0), ADC_DT_SPEC_GET_BY_IDX(USER, 1), ADC_DT_SPEC_GET_BY_IDX(USER, 2),
	ADC_DT_SPEC_GET_BY_IDX(USER, 3),          /* moisture divider midpoint; not a pp_adc_channel_t */
};
#define ADC_MOISTURE 3
static const struct pwm_dt_spec led_pwm = PWM_DT_SPEC_GET_BY_NAME(USER, led);
static const struct pwm_dt_spec us_a = PWM_DT_SPEC_GET_BY_NAME(USER, us_a);
static const struct pwm_dt_spec us_b = PWM_DT_SPEC_GET_BY_NAME(USER, us_b);
static const struct pwm_dt_spec us_level = PWM_DT_SPEC_GET_BY_NAME(USER, us_level);
static const struct gpio_dt_spec moist_drv = GPIO_DT_SPEC_GET(USER, moist_drv_gpios);
static const struct gpio_dt_spec us_en = GPIO_DT_SPEC_GET(USER, us_en_gpios);
static const struct gpio_dt_spec alert = GPIO_DT_SPEC_GET(USER, alert_gpios);
static const struct gpio_dt_spec button = GPIO_DT_SPEC_GET(USER, button_gpios);
static const struct gpio_dt_spec status = GPIO_DT_SPEC_GET(USER, status_gpios);

K_MSGQ_DEFINE(command_queue, 64, 4, 1);      /* text lines received over Bluetooth */
static app_t app;

/* ---- pp_hal.h ---- */

int hal_i2c_write(uint8_t addr, const uint8_t *data, size_t len)
{
	return i2c_write(i2c, data, len, addr);
}

int hal_i2c_write_read(uint8_t addr, const uint8_t *wr, size_t wr_len, uint8_t *rd, size_t rd_len)
{
	return i2c_write_read(i2c, addr, wr, wr_len, rd, rd_len);
}

static int adc_read_uv(int channel, int32_t *microvolts)
{
	int16_t raw = 0;
	int32_t mv;
	struct adc_sequence seq = { .buffer = &raw, .buffer_size = sizeof(raw) };
	int err = adc_sequence_init_dt(&adc[channel], &seq);

	if (err == 0) {
		err = adc_read(adc[channel].dev, &seq);
	}
	if (err == 0) {
		mv = raw;
		err = adc_raw_to_millivolts_dt(&adc[channel], &mv);
		*microvolts = mv * 1000;
	}
	return err;
}

int hal_adc_read_uv(pp_adc_channel_t channel, int32_t *microvolts)
{
	return adc_read_uv((int)channel, microvolts);
}

int hal_moisture_measure_uv(int32_t *swing_uv)
{
	/* Toggle the drive pin at about 1 kHz and sample the divider midpoint in each half cycle. */
	int64_t sum = 0;
	int32_t high, low;

	for (int i = 0; i < MOISTURE_CYCLES; i++) {
		gpio_pin_set_dt(&moist_drv, 1);
		k_busy_wait(250);
		if (adc_read_uv(ADC_MOISTURE, &high) != 0) {
			gpio_pin_set_dt(&moist_drv, 0);
			return -1;
		}
		k_busy_wait(150);
		gpio_pin_set_dt(&moist_drv, 0);
		k_busy_wait(250);
		if (adc_read_uv(ADC_MOISTURE, &low) != 0) {
			return -1;
		}
		k_busy_wait(150);
		sum += high - low;
	}
	*swing_uv = (int32_t)(sum / MOISTURE_CYCLES);
	return 0;
}

void hal_led_set_permille(uint16_t duty)
{
	pwm_set_dt(&led_pwm, PWM_USEC(LED_PERIOD_US), PWM_USEC((uint32_t)duty * LED_PERIOD_US / 1000u));
}

void hal_ultrasound_set(uint16_t amplitude)
{
	/* Strength: the boost output is about 9.95 V minus 1.515 x the control voltage, so amplitude 1000
	 * (10 V) needs 0 V of control and amplitude 500 (5 V) needs about 3.3 V.
	 * Drive: two complementary 50% square waves on the H-bridge inputs; the enable line powers the boost. */
	uint32_t target_mv = (uint32_t)amplitude * 10u;
	uint32_t control_mv = target_mv >= 9950u ? 0u : (9950u - target_mv) * 1000u / 1515u;
	uint32_t pulse = amplitude ? US_PERIOD_NS / 2 : 0;

	if (control_mv > 3300u) {
		control_mv = 3300u;
	}
	pwm_set_dt(&us_level, PWM_USEC(LEVEL_PERIOD_US), PWM_USEC(control_mv * LEVEL_PERIOD_US / 3300u));
	pwm_set_dt(&us_a, US_PERIOD_NS, pulse);
	pwm_set_dt(&us_b, US_PERIOD_NS, pulse);
	gpio_pin_set_dt(&us_en, amplitude > 0);
}

bool hal_temp_alert_active(void)
{
	return gpio_pin_get_dt(&alert) > 0;
}

void hal_status_led(bool on)
{
	gpio_pin_set_dt(&status, on);
}

void hal_delay_ms(uint32_t ms)
{
	k_msleep(ms);
}

void hal_link_write(const char *line)
{
	printk("%s", line);
	(void)bt_nus_send(NULL, (const uint8_t *)line, strlen(line));
}

/* ---- Bluetooth ---- */

static void nus_received(struct bt_conn *conn, const uint8_t *const data, uint16_t len)
{
	char line[64] = { 0 };

	ARG_UNUSED(conn);
	memcpy(line, data, MIN(len, sizeof(line) - 1));
	(void)k_msgq_put(&command_queue, line, K_NO_WAIT);
}

static struct bt_nus_cb nus_callbacks = { .received = nus_received };

static const struct bt_data adv[] = {
	BT_DATA_BYTES(BT_DATA_FLAGS, (BT_LE_AD_GENERAL | BT_LE_AD_NO_BREDR)),
	BT_DATA(BT_DATA_NAME_COMPLETE, CONFIG_BT_DEVICE_NAME, sizeof(CONFIG_BT_DEVICE_NAME) - 1),
};
static const struct bt_data scan_response[] = {
	BT_DATA_BYTES(BT_DATA_UUID128_ALL, BT_UUID_NUS_VAL),
};

int main(void)
{
	char line[64];
	bool was_pressed = false;

	if (!device_is_ready(i2c)) {
		printk("i2c not ready\n");
		return 0;
	}
	gpio_pin_configure_dt(&us_en, GPIO_OUTPUT_INACTIVE);
	gpio_pin_configure_dt(&status, GPIO_OUTPUT_INACTIVE);
	gpio_pin_configure_dt(&moist_drv, GPIO_OUTPUT_INACTIVE);
	gpio_pin_configure_dt(&alert, GPIO_INPUT);
	gpio_pin_configure_dt(&button, GPIO_INPUT);
	for (size_t i = 0; i < ARRAY_SIZE(adc); i++) {
		adc_channel_setup_dt(&adc[i]);
	}
	if (bt_enable(NULL) == 0 && bt_nus_init(&nus_callbacks) == 0) {
		bt_le_adv_start(BT_LE_ADV_CONN, adv, ARRAY_SIZE(adv), scan_response, ARRAY_SIZE(scan_response));
	}

	app_init(&app, k_uptime_get_32());
	for (;;) {
		bool pressed = gpio_pin_get_dt(&button) > 0;

		while (k_msgq_get(&command_queue, line, K_NO_WAIT) == 0) {
			app_command(&app, k_uptime_get_32(), line);
		}
		if (pressed && !was_pressed) {
			hal_link_write("B,1,0,0\n");     /* the wearer pressed the pain / odour button */
		}
		was_pressed = pressed;
		app_tick(&app, k_uptime_get_32());
		k_msleep(250);
	}
	return 0;
}
